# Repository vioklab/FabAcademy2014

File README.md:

FabAcademy2014
==============

FabAcademy 2014 download files

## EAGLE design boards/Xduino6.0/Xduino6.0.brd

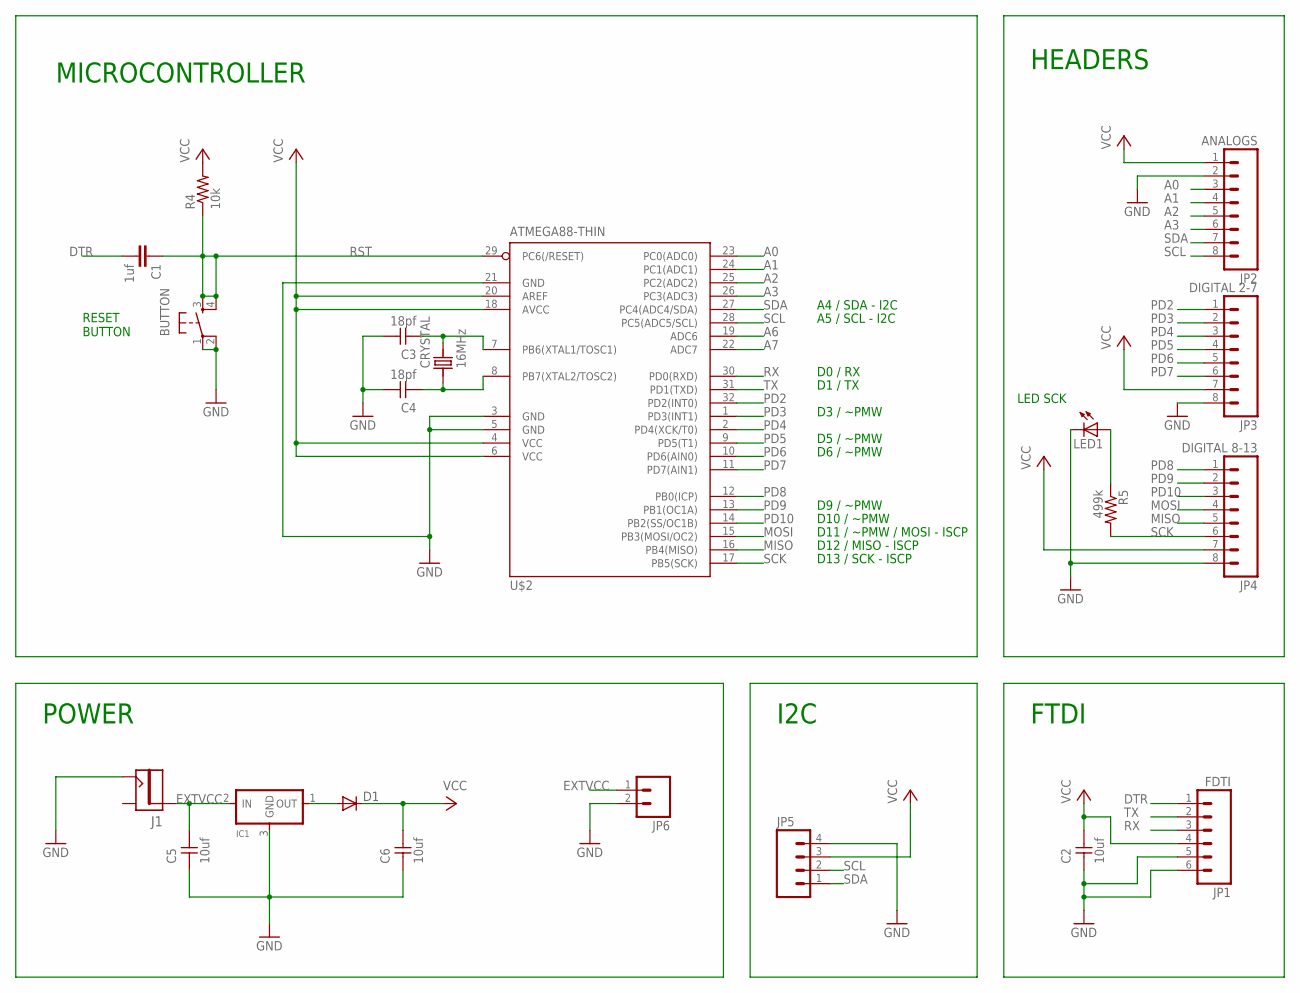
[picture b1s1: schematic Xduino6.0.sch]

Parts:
BUTTON: 6MM_SWITCH6MM_SWITCH; 6MM_SWITCH
C1: 1uf; 1206
C2, C5, C6: 10uf; 1206
C3, C4: 18pf; 1206
CRYSTAL: 16MHz; CS10
D1: DIODESOD123; SOD123
IC1: REGULATORSOT23; SOT23
J1: JACK.65MM; JACK_.65MM
JP1: FDTI; 1X06-SMD_EDGE
JP2: ANALOGS; 1X08
JP3: DIGITAL 2-7; 1X08
JP4: DIGITAL 8-13; 1X08
JP5: M04PTH; 1X04
JP6: M02PTH; 1X02
LED1: LED1206; 1206
R4: 10k; 1206
R5: 499k; 1206
U$2: ATMEGA88-THIN; TQFP32-08THIN

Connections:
A0: JP2.3, U$2.23 (PC0(ADC0))
A1: JP2.4, U$2.24 (PC1(ADC1))
A2: JP2.5, U$2.25 (PC2(ADC2))
A3: JP2.6, U$2.26 (PC3(ADC3))
A6: U$2.19 (ADC6)
A7: U$2.22 (ADC7)
DTR: C1.2, JP1.1
EXTVCC: C5.2, IC1.2 (IN), J1.PIN, JP6.1
GND: BUTTON.1, BUTTON.2 (P1), C2.1, C3.2, C4.2, C5.1, C6.1, IC1.3 (GND), J1.SHUNT (CONTACT), JP1.5, JP1.6, JP2.2, JP3.8, JP4.8, JP5.4, JP6.2, LED1.2 (C), U$2.3 (GND), U$2.5 (GND), U$2.21 (GND)
MISO: JP4.5, U$2.16 (PB4(MISO))
MOSI: JP4.4, U$2.15 (PB3(MOSI/OC2))
unnamed: LED1.1 (A), R5.1
unnamed: C4.1, CRYSTAL.P$1 (1), U$2.8 (PB7(XTAL2/TOSC2))
unnamed: C3.1, CRYSTAL.P$2 (2), U$2.7 (PB6(XTAL1/TOSC1))
unnamed: D1.ANODE (A), IC1.1 (OUT)
PD2: JP3.1, U$2.32 (PD2(INT0))
PD3: JP3.2, U$2.1 (PD3(INT1))
PD4: JP3.3, U$2.2 (PD4(XCK/T0))
PD5: JP3.4, U$2.9 (PD5(T1))
PD6: JP3.5, U$2.10 (PD6(AIN0))
PD7: JP3.6, U$2.11 (PD7(AIN1))
PD8: JP4.1, U$2.12 (PB0(ICP))
PD9: JP4.2, U$2.13 (PB1(OC1A))
PD10: JP4.3, U$2.14 (PB2(SS/OC1B))
RST: BUTTON.3 (S), BUTTON.4 (S1), C1.1, R4.1, U$2.29 (PC6(/RESET))
RX: JP1.3, U$2.30 (PD0(RXD))
SCK: JP4.6, R5.2, U$2.17 (PB5(SCK))
SCL: JP2.8, JP5.2, U$2.28 (PC5(ADC5/SCL))
SDA: JP2.7, JP5.1, U$2.27 (PC4(ADC4/SDA))
TX: JP1.2, U$2.31 (PD1(TXD))
VCC: C2.2, C6.2, D1.CATHODE (C), JP1.4, JP2.1, JP3.7, JP4.7, JP5.3, R4.2, U$2.4 (VCC), U$2.6 (VCC), U$2.18 (AVCC), U$2.20 (AREF)

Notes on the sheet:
D5 / ~PMW
D6 / ~PMW
D9 / ~PMW
D10 / ~PMW
D11 / ~PMW / MOSI - ISCP
D12 / MISO - ISCP
D13 / SCK - ISCP
D0 / RX
A4 / SDA - I2C
A5 / SCL - I2C
D1 / TX
D3 / ~PMW
RESET BUTTON
MICROCONTROLLER
FTDI
HEADERS
LED SCK
POWER
I2C

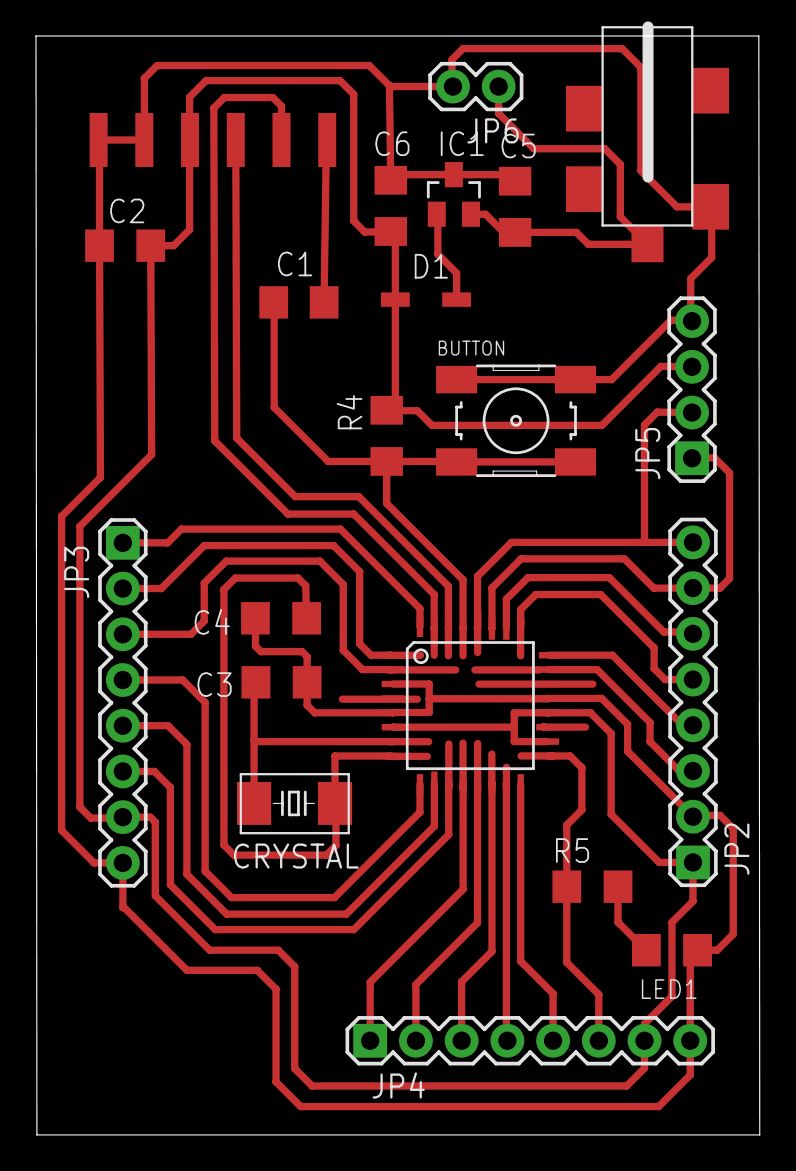
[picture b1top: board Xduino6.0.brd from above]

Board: 2 copper layers, 40.2 x 61.1 mm, 21 parts (0 on the bottom side), 29 nets.

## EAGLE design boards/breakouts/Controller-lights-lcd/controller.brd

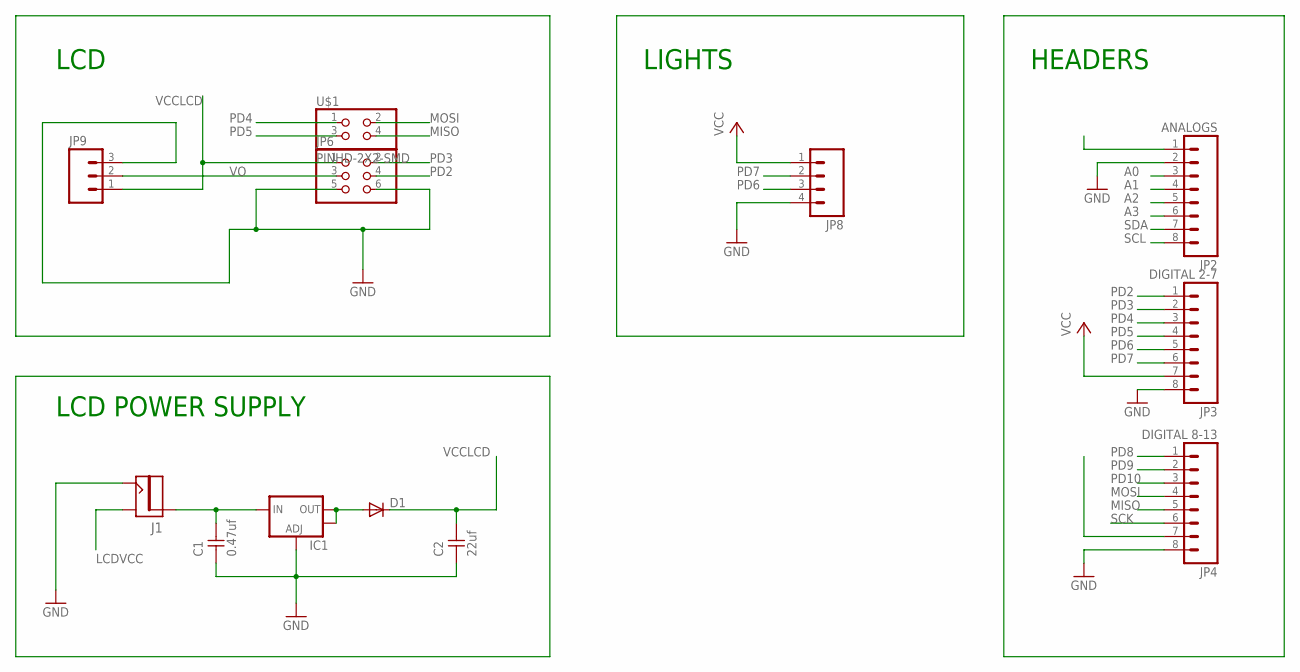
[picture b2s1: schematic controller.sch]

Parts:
C1: 0.47uf; 1206
C2: 22uf; 1206
D1: DIODESOD123; SOD123
IC1: V_REG_LM1117SOT223; SOT223
J1: JACK.65MM; JACK_.65MM
JP2: ANALOGS; 1X08
JP3: DIGITAL 2-7; 1X08
JP4: DIGITAL 8-13; 1X08
JP6: PINHD-2X3-SMD; 2X03SMD
JP8: M04PTH; 1X04
JP9: M03PTH; 1X03
U$1: PINHD-2X2-SMD; 2X02SMD

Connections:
A0: JP2.3
A1: JP2.4
A2: JP2.5
A3: JP2.6
GND: C1.1, C2.1, IC1.1 (ADJ), J1.SHUNT (CONTACT), JP2.2, JP3.8, JP4.8, JP6.5, JP6.6, JP8.4, JP9.3
LCDVCC: J1.CONTACT (SHUNT)
MISO: JP4.5, U$1.4
MOSI: JP4.4, U$1.2
unnamed: C1.2, IC1.3 (IN), J1.PIN
unnamed: D1.ANODE (A), IC1.2 (OUT), IC1.4 (OUT)
PD2: JP3.1, JP6.4
PD3: JP3.2, JP6.2
PD4: JP3.3, U$1.1
PD5: JP3.4, U$1.3
PD6: JP3.5, JP8.3
PD7: JP3.6, JP8.2
PD8: JP4.1
PD9: JP4.2
PD10: JP4.3
SCK: JP4.6
SCL: JP2.8
SDA: JP2.7
VCC: JP3.7, JP8.1
VCCLCD: C2.2, D1.CATHODE (C), JP6.1, JP9.1
VO: JP6.3, JP9.2

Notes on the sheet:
HEADERS
LCD
LIGHTS
LCD POWER SUPPLY

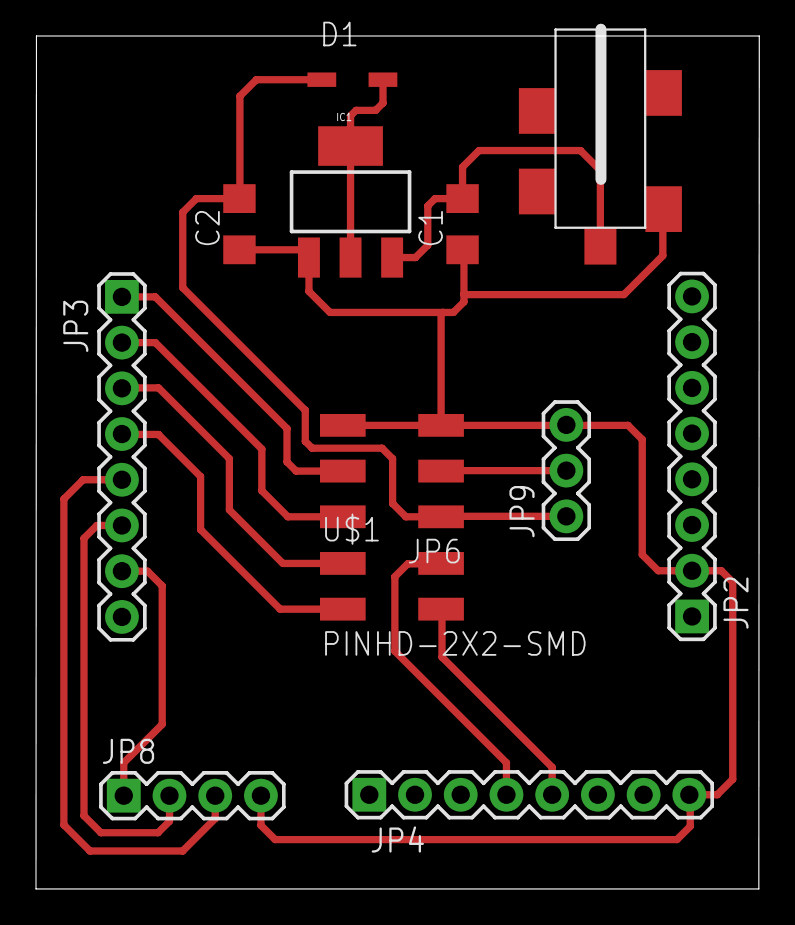
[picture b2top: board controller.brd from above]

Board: 2 copper layers, 40.2 x 47.4 mm, 12 parts (0 on the bottom side), 14 nets.

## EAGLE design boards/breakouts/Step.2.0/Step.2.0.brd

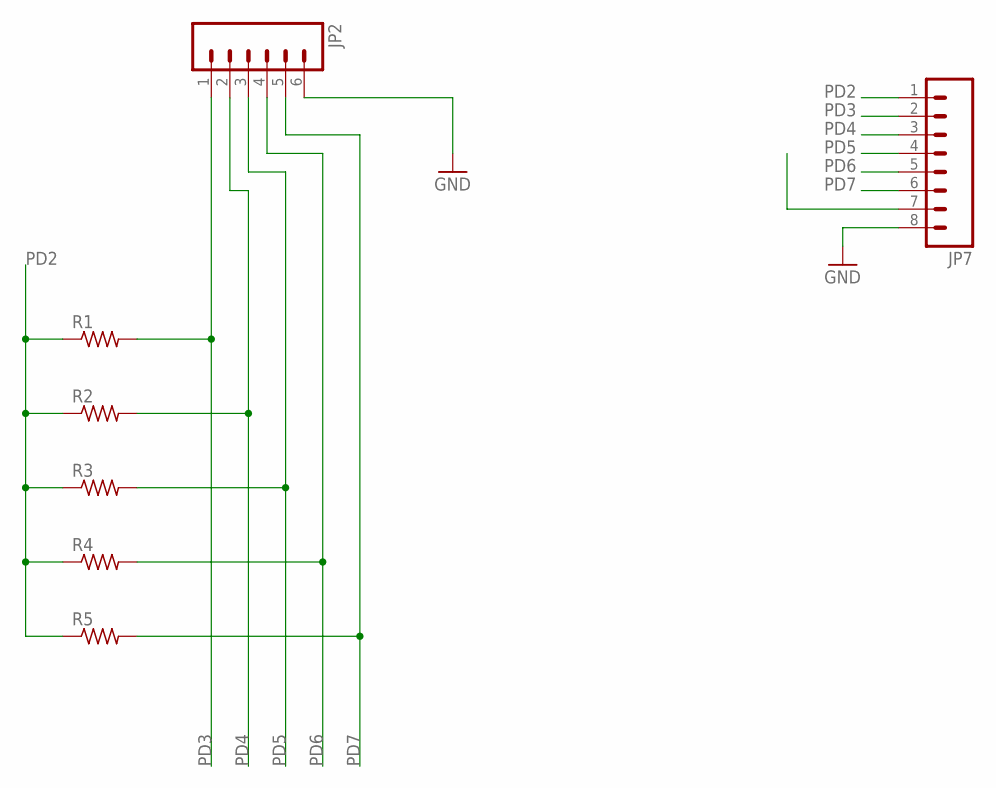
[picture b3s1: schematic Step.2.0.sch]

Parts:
JP2: M06SIP; 1X06
JP7: M08; 1X08
R1, R2, R3, R4, R5: RESISTOR1206; 1206

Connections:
GND: JP2.6, JP7.8
PD2: JP7.1, R1.1, R2.1, R3.1, R4.1, R5.1
PD3: JP2.1, JP7.2, R1.2
PD4: JP2.2, JP7.3, R2.2
PD5: JP2.3, JP7.4, R3.2
PD6: JP2.4, JP7.5, R4.2
PD7: JP2.5, JP7.6, R5.2

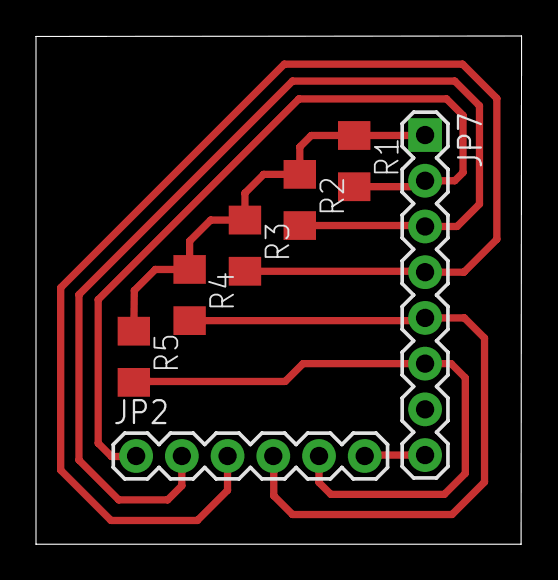
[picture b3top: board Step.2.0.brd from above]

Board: 2 copper layers, 27.0 x 28.2 mm, 7 parts (0 on the bottom side), 7 nets.

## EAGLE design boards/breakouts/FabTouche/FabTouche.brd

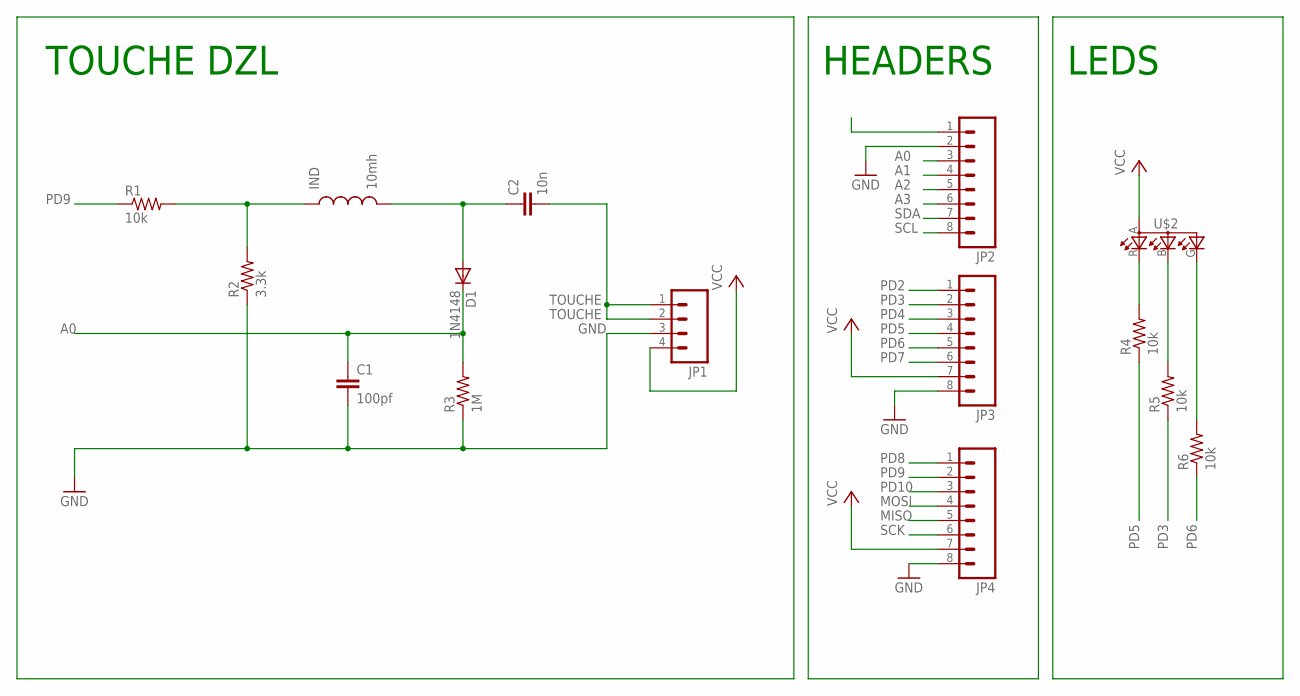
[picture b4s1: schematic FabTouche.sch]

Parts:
C1: 100pf; 1206
C2: 10n; 1206
D1: 1N4148; SOD123
IND: 10mh; CDRH3D28
JP1: M04PTH; 1X04
JP2, JP3, JP4: M08; 1X08
R1, R4, R5, R6: 10k; 1206
R2: 3.3k; 1206
R3: 1M; 1206
U$2: LEDRGBOLD; P-LCC-4-3

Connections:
A0: C1.1, D1.CATHODE (C), JP2.3, R3.2
A1: JP2.4
A2: JP2.5
A3: JP2.6
GND: C1.2, JP1.3, JP2.2, JP3.8, JP4.8, R2.1, R3.1
MISO: JP4.5
MOSI: JP4.4
unnamed: C2.1, D1.ANODE (A), IND.2
unnamed: IND.1, R1.2, R2.2
unnamed: R4.2, U$2.R (CRED)
unnamed: R5.2, U$2.B (CBLUE)
unnamed: R6.2, U$2.G (CGREEN)
PD2: JP3.1
PD3: JP3.2, R5.1
PD4: JP3.3
PD5: JP3.4, R4.1
PD6: JP3.5, R6.1
PD7: JP3.6
PD8: JP4.1
PD9: JP4.2, R1.1
PD10: JP4.3
SCK: JP4.6
SCL: JP2.8
SDA: JP2.7
TOUCHE: C2.2, JP1.1, JP1.2
VCC: JP1.4, JP3.7, JP4.7, U$2.A (A2)

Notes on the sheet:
HEADERS
TOUCHE DZL
LEDS

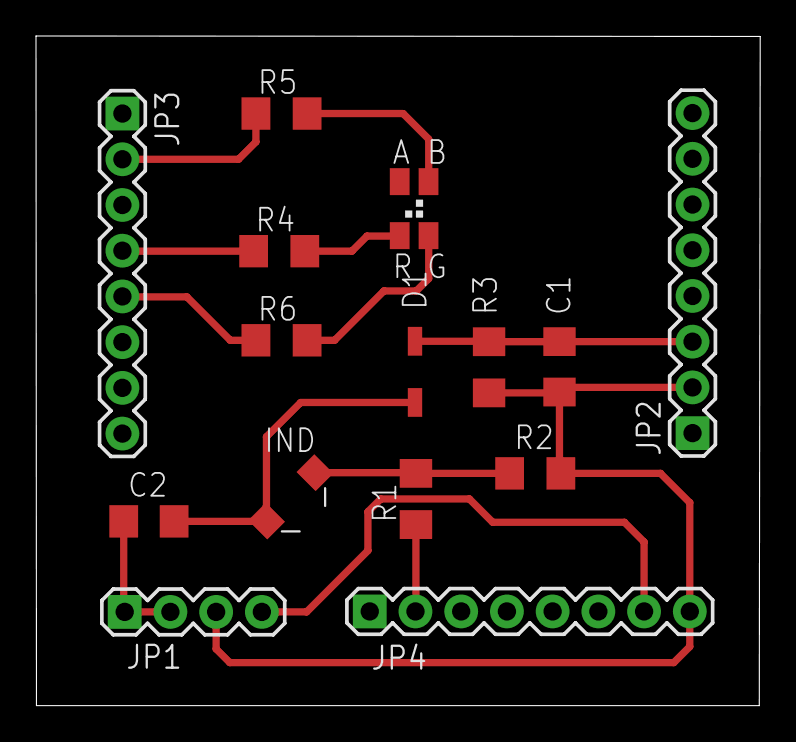
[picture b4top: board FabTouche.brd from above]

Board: 2 copper layers, 40.2 x 37.2 mm, 15 parts (0 on the bottom side), 13 nets.

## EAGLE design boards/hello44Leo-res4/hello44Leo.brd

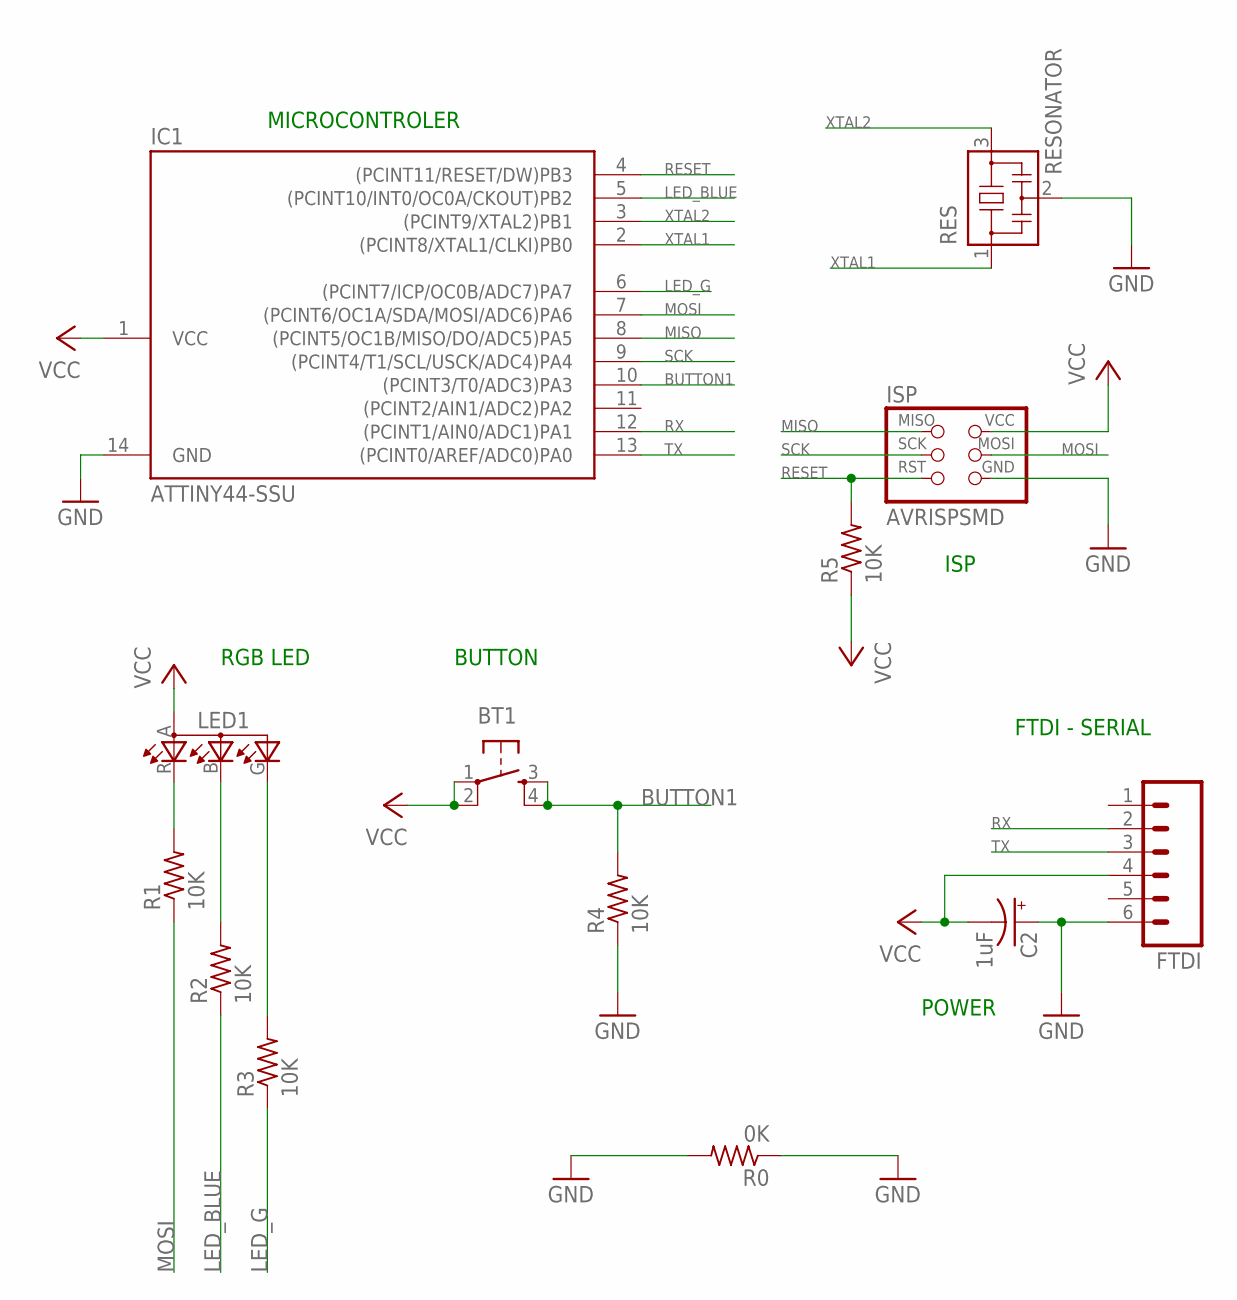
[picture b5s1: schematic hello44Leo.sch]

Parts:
BT1: 6MM_SWITCH6MM_SWITCH; 6MM_SWITCH
C2: 1uF; A3216-18
FTDI: M061X06-SMD_EDGE_FEMALE; 1X06-SMD_EDGE
IC1: ATTINY44-SSU; SOIC14
ISP: AVRISPSMD; 2X03SMD
LED1: LEDRGBOLD; P-LCC-4-3
R0: 0K; 1206
R1, R2, R3, R4, R5: 10K; 1206
RES: RESONATOR; EFOBM

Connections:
BUTTON1: BT1.3 (S), BT1.4 (S1), IC1.10 ((PCINT3/T0/ADC3)PA3), R4.2
GND: C2.+, FTDI.6, IC1.14 (GND), ISP.6 (GND), R0.1, R0.2, R4.1, RES.2
LED_BLUE: IC1.5 ((PCINT10/INT0/OC0A/CKOUT)PB2), R2.1
LED_G: IC1.6 ((PCINT7/ICP/OC0B/ADC7)PA7), R3.1
MISO: IC1.8 ((PCINT5/OC1B/MISO/DO/ADC5)PA5), ISP.1 (MISO)
MOSI: IC1.7 ((PCINT6/OC1A/SDA/MOSI/ADC6)PA6), ISP.4 (MOSI), R1.1
unnamed: LED1.R (CRED), R1.2
unnamed: LED1.B (CBLUE), R2.2
unnamed: LED1.G (CGREEN), R3.2
RESET: IC1.4 ((PCINT11/RESET/DW)PB3), ISP.5 (RST), R5.2
RX: FTDI.2, IC1.12 ((PCINT1/AIN0/ADC1)PA1)
SCK: IC1.9 ((PCINT4/T1/SCL/USCK/ADC4)PA4), ISP.3 (SCK)
TX: FTDI.3, IC1.13 ((PCINT0/AREF/ADC0)PA0)
VCC: BT1.1, BT1.2 (P1), C2.-, FTDI.4, IC1.1 (VCC), ISP.2 (VCC), LED1.A (A2), R5.1
XTAL1: IC1.2 ((PCINT8/XTAL1/CLKI)PB0), RES.1
XTAL2: IC1.3 ((PCINT9/XTAL2)PB1), RES.3

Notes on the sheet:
ISP
MICROCONTROLER
RGB LED
BUTTON
FTDI - SERIAL
POWER

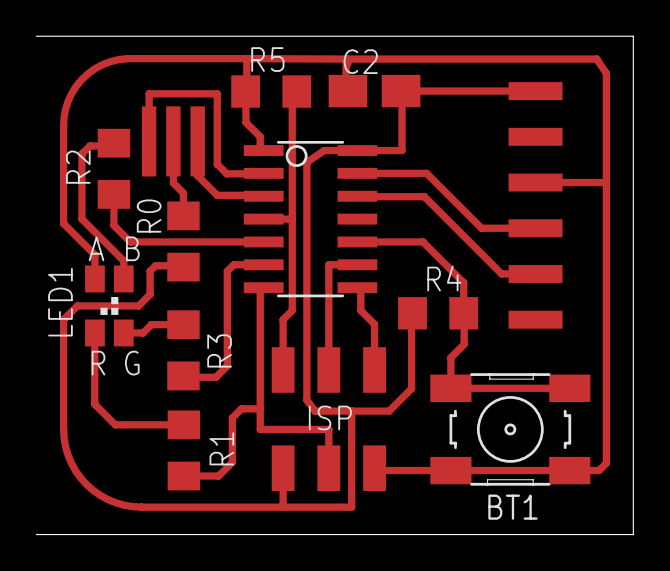
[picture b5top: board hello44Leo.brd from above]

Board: 2 copper layers, 33.2 x 27.7 mm, 13 parts (0 on the bottom side), 16 nets.

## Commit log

2014-06-05 Download Files
    Changing from dropbox to github
2014-06-05 Documentation - website
    Documentation - website
2014-06-05 Unziped version
2014-06-05 Wall Pot unzip
2014-06-05 unziped
2014-06-05 Download Files
2014-06-07 Download Files
    Networking Communication
2014-06-07 Download Files
    New Xduino6 Files
2014-06-08 Download Files
    Composites Files
2014-06-09 Download Files
    Added BOM PDF
2014-06-09 Download Files
    BOM Stimuli
2014-06-09 Download Files
    Updating BOM files
2014-06-09 Download Files
    Updating Folder Name
2014-06-10 Download Files
    UI files
2014-06-10 Download Files
    Plant Stimuli design
2014-06-10 Download Files
    Boards And Sofware
2014-06-11 Download Files
    New Final Documentation
2014-06-14 Download Files
    Bom Files

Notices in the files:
parts and their libraries:
01_SparkFun: Licensing: CC v3.0 Share-Alike You are welcome to use this library for commercial purposes.
